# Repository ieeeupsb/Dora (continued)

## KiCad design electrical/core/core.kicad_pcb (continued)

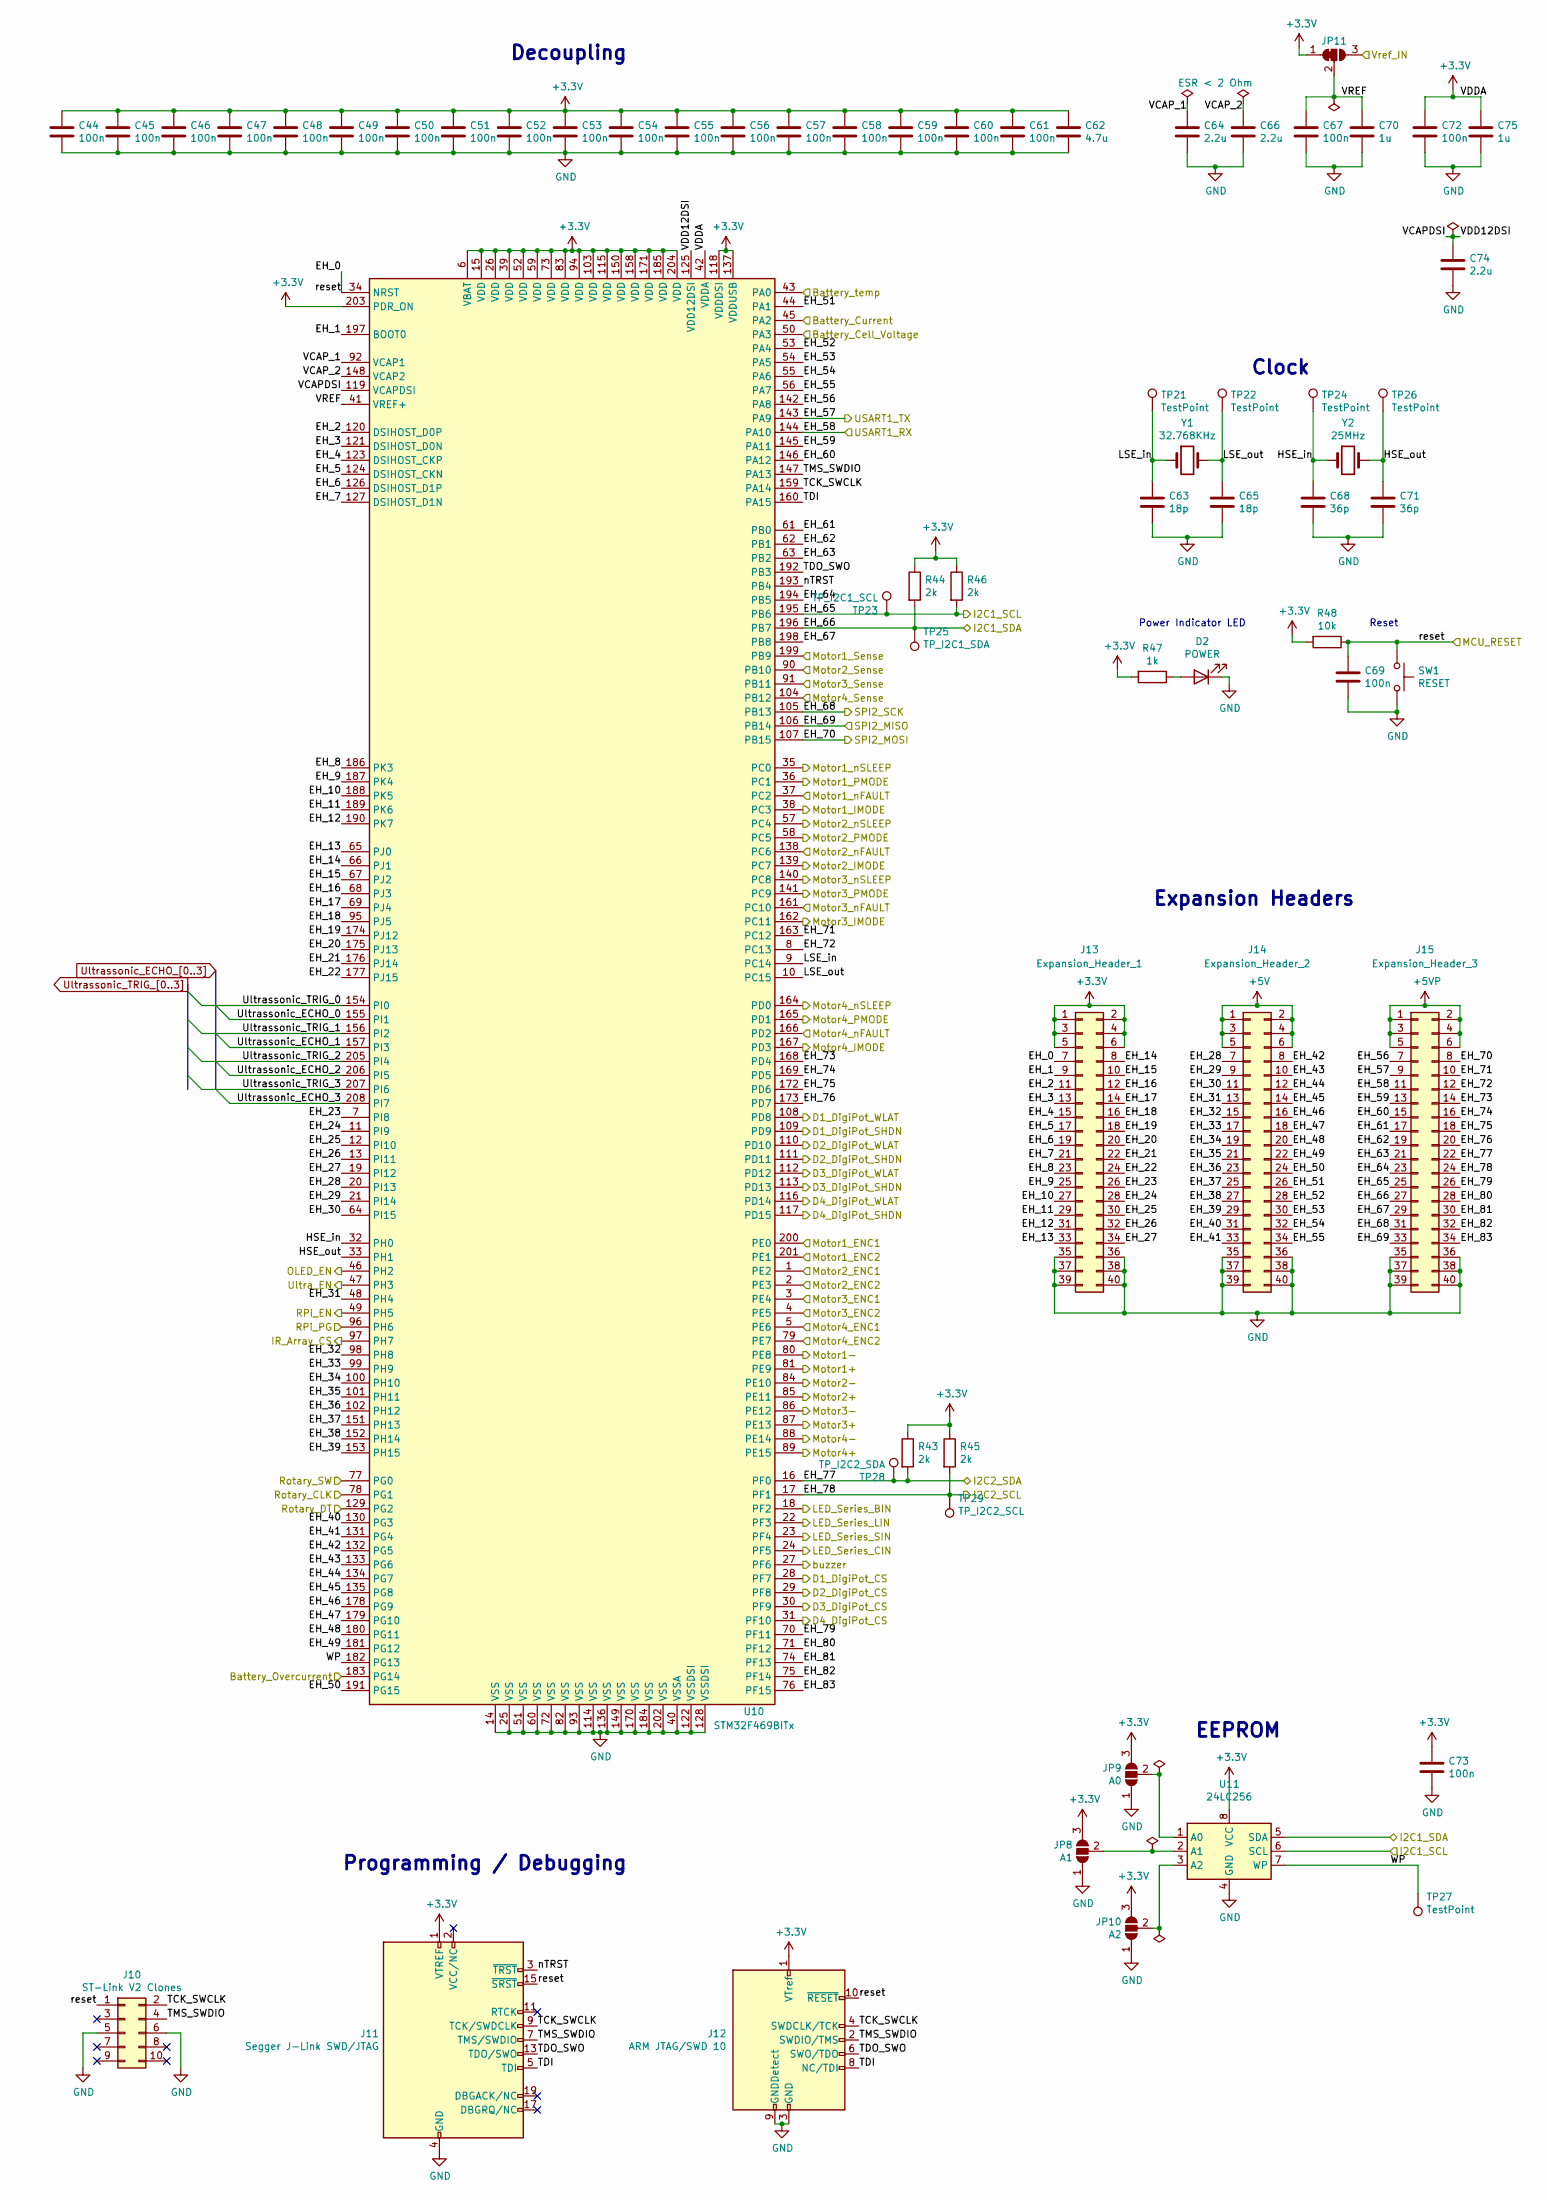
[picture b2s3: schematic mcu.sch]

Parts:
C44, C45, C46, C47, C48, C49, C50, C51, C52, C53, C54, C55, C56, C57, C58, C59, C60, C61, C67, C69, C72, C73: 100n; C_0603_1608Metric
C62: 4.7u; C_0603_1608Metric
C63, C65: 18p; C_0603_1608Metric
C64, C66, C74: 2.2u; C_0603_1608Metric
C68, C71: 36p; C_0603_1608Metric
C70, C75: 1u; C_0603_1608Metric
D2: POWER; LED_0805_2012Metric
J10: ST-Link V2 Clones; IDC-Header_2x05_P2.54mm_Vertical
J11: Segger J-Link SWD/JTAG; IDC-Header_2x10_P2.54mm_Vertical
J12: ARM JTAG/SWD 10; IDC-Header_2x05_P2.54mm_Vertical
J13: Expansion_Header_1; IDC-Header_2x20_P2.54mm_Vertical
J14: Expansion_Header_2; IDC-Header_2x20_P2.54mm_Vertical
J15: Expansion_Header_3; IDC-Header_2x20_P2.54mm_Vertical
JP8: A1; SolderJumper-3_P1.3mm_Open_Pad1.0x1.5mm
JP9: A0; SolderJumper-3_P1.3mm_Open_Pad1.0x1.5mm
JP10: A2; SolderJumper-3_P1.3mm_Open_Pad1.0x1.5mm
JP11: Vref_select; SolderJumper-3_P1.3mm_Bridged12_RoundedPad1.0x1.5mm_NumberL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
R43, R44, R45, R46: 2k; R_0603_1608Metric
R47: 1k; R_0603_1608Metric
R48: 10k; R_0603_1608Metric
SW1: RESET; SW_PUSH_6mm
TP21, TP22, TP24, TP26, TP27: TestPoint; TestPoint_Pad_D1.0mm
TP23: TP_I2C1_SCL; TestPoint_Pad_D1.0mm
TP25: TP_I2C1_SDA; TestPoint_Pad_D1.0mm
TP28: TP_I2C2_SDA; TestPoint_Pad_D1.0mm
TP29: TP_I2C2_SCL; TestPoint_Pad_D1.0mm
U10: STM32F469BITx; LQFP-208_28x28mm_P0.5mm
U11: 24LC256; SOIC-8_3.9x4.9mm_P1.27mm
Y1: 32.768KHz; Crystal_SMD_2520-4Pin_2.5x2.0mm
Y2: 25MHz; Crystal_SMD_2520-4Pin_2.5x2.0mm

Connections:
+3V3: C44.1, C45.1, C46.1, C47.1, C48.1, C49.1, C50.1, C51.1, C52.1, C53.1, C54.1, C55.1, C56.1, C57.1, C58.1, C59.1, C60.1, C61.1, C62.1, C72.1, C73.1, C75.1, J11.1 (VTREF), J12.1 (VTref), J13.1, J13.2, J13.3, J13.4, J13.5, J13.6, JP8.3 (B), JP9.3 (B), JP10.3 (B), JP11.1 (A), R43.1, R44.1, R45.1, R46.1, R47.2, R48.2, U10.6 (VBAT), U10.15 (VDD), U10.26 (VDD), U10.39 (VDD), U10.42 (VDDA), U10.52 (VDD), U10.59 (VDD), U10.73 (VDD), U10.83 (VDD), U10.94 (VDD), U10.103 (VDD), U10.115 (VDD), U10.118 (VDDDSI), U10.137 (VDDUSB), U10.150 (VDD), U10.158 (VDD), U10.171 (VDD), U10.185 (VDD), U10.203 (PDR_ON), U10.204 (VDD), U11.8 (VCC); also elsewhere on the board
+5V: J14.1, J14.2, J14.3, J14.4, J14.5, J14.6; also elsewhere on the board
+5VP: J15.1, J15.2, J15.3, J15.4, J15.5, J15.6; also elsewhere on the board
/Battery_Cell_Voltage: U10.50 (PA3); also elsewhere on the board
/Battery_Current: U10.45 (PA2); also elsewhere on the board
/Battery_Overcurrent: U10.183 (PG14); also elsewhere on the board
/Battery_Temperature: U10.43 (PA0); also elsewhere on the board
/D1_DigiPot_CS: U10.28 (PF7); also elsewhere on the board
/D1_DigiPot_SHDN: U10.109 (PD9); also elsewhere on the board
/D1_DigiPot_WLAT: U10.108 (PD8); also elsewhere on the board
/D1_IMODE: U10.38 (PC3); also elsewhere on the board
/D1_IN1: U10.80 (PE8); also elsewhere on the board
/D1_IN2: U10.81 (PE9); also elsewhere on the board
/D1_PMODE: U10.36 (PC1); also elsewhere on the board
/D1_SENSE: U10.199 (PB9); also elsewhere on the board
/D1_nFAULT: U10.37 (PC2); also elsewhere on the board
/D1_nSLEEP: U10.35 (PC0); also elsewhere on the board
/D2_DigiPot_CS: U10.29 (PF8); also elsewhere on the board
/D2_DigiPot_SHDN: U10.111 (PD11); also elsewhere on the board
/D2_DigiPot_WLAT: U10.110 (PD10); also elsewhere on the board
/D2_IMODE: U10.139 (PC7); also elsewhere on the board
/D2_IN1: U10.84 (PE10); also elsewhere on the board
/D2_IN2: U10.85 (PE11); also elsewhere on the board
/D2_PMODE: U10.58 (PC5); also elsewhere on the board
/D2_SENSE: U10.90 (PB10); also elsewhere on the board
/D2_nFAULT: U10.138 (PC6); also elsewhere on the board
/D2_nSLEEP: U10.57 (PC4); also elsewhere on the board
/D3_DigiPot_CS: U10.30 (PF9); also elsewhere on the board
/D3_DigiPot_SHDN: U10.113 (PD13); also elsewhere on the board
/D3_DigiPot_WLAT: U10.112 (PD12); also elsewhere on the board
/D3_IMODE: U10.162 (PC11); also elsewhere on the board
/D3_IN1: U10.86 (PE12); also elsewhere on the board
/D3_IN2: U10.87 (PE13); also elsewhere on the board
/D3_PMODE: U10.141 (PC9); also elsewhere on the board
/D3_SENSE: U10.91 (PB11); also elsewhere on the board
/D3_nFAULT: U10.161 (PC10); also elsewhere on the board
/D3_nSLEEP: U10.140 (PC8); also elsewhere on the board
/D4_DigiPot_CS: U10.31 (PF10); also elsewhere on the board
/D4_DigiPot_SHDN: U10.117 (PD15); also elsewhere on the board
/D4_DigiPot_WLAT: U10.116 (PD14); also elsewhere on the board
/D4_IMODE: U10.167 (PD3); also elsewhere on the board
/D4_IN1: U10.88 (PE14); also elsewhere on the board
/D4_IN2: U10.89 (PE15); also elsewhere on the board
/D4_PMODE: U10.165 (PD1); also elsewhere on the board
/D4_SENSE: U10.104 (PB12); also elsewhere on the board
/D4_nFAULT: U10.166 (PD2); also elsewhere on the board
/D4_nSLEEP: U10.164 (PD0); also elsewhere on the board
/I2C1_SCL: J15.25, R46.2, TP23.1, U10.195 (PB6), U11.6 (SCL); also elsewhere on the board
/I2C1_SDA: J15.27, R44.2, TP25.1, U10.196 (PB7), U11.5 (SDA); also elsewhere on the board
/I2C2_SCL: J15.24, R45.2, TP29.1, U10.17 (PF1); also elsewhere on the board
/I2C2_SDA: J15.22, R43.2, TP28.1, U10.16 (PF0); also elsewhere on the board
/IR_Array_CS: U10.97 (PH7); also elsewhere on the board
/LED_Series_BIN: U10.18 (PF2); also elsewhere on the board
/LED_Series_CIN: U10.24 (PF5); also elsewhere on the board
/LED_Series_LIN: U10.22 (PF3); also elsewhere on the board
/LED_Series_SIN: U10.23 (PF4); also elsewhere on the board
/MCU/EH_1: J13.9, U10.197 (BOOT0)
/MCU/EH_2: J13.11, U10.120 (DSIHOST_D0P)
/MCU/EH_3: J13.13, U10.121 (DSIHOST_D0N)
/MCU/EH_4: J13.15, U10.123 (DSIHOST_CKP)
/MCU/EH_5: J13.17, U10.124 (DSIHOST_CKN)
/MCU/EH_6: J13.19, U10.126 (DSIHOST_D1P)
/MCU/EH_7: J13.21, U10.127 (DSIHOST_D1N)
/MCU/EH_8: J13.23, U10.186 (PK3)
/MCU/EH_9: J13.25, U10.187 (PK4)
/MCU/EH_10: J13.27, U10.188 (PK5)
/MCU/EH_11: J13.29, U10.189 (PK6)
/MCU/EH_12: J13.31, U10.190 (PK7)
/MCU/EH_13: J13.33, U10.65 (PJ0)
/MCU/EH_14: J13.8, U10.66 (PJ1)
/MCU/EH_15: J13.10, U10.67 (PJ2)
/MCU/EH_16: J13.12, U10.68 (PJ3)
/MCU/EH_17: J13.14, U10.69 (PJ4)
/MCU/EH_18: J13.16, U10.95 (PJ5)
/MCU/EH_19: J13.18, U10.174 (PJ12)
/MCU/EH_20: J13.20, U10.175 (PJ13)
/MCU/EH_21: J13.22, U10.176 (PJ14)
/MCU/EH_22: J13.24, U10.177 (PJ15)
/MCU/EH_23: J13.26, U10.7 (PI8)
/MCU/EH_24: J13.28, U10.11 (PI9)
/MCU/EH_25: J13.30, U10.12 (PI10)
/MCU/EH_26: J13.32, U10.13 (PI11)
/MCU/EH_27: J13.34, U10.19 (PI12)
/MCU/EH_28: J14.7, U10.20 (PI13)
/MCU/EH_29: J14.9, U10.21 (PI14)
/MCU/EH_30: J14.11, U10.64 (PI15)
/MCU/EH_31: J14.13, U10.48 (PH4)
/MCU/EH_32: J14.15, U10.98 (PH8)
/MCU/EH_33: J14.17, U10.99 (PH9)
/MCU/EH_34: J14.19, U10.100 (PH10)
/MCU/EH_35: J14.21, U10.101 (PH11)
/MCU/EH_36: J14.23, U10.102 (PH12)
/MCU/EH_37: J14.25, U10.151 (PH13)
/MCU/EH_38: J14.27, U10.152 (PH14)
/MCU/EH_39: J14.29, U10.153 (PH15)
/MCU/EH_40: J14.31, U10.130 (PG3)
/MCU/EH_41: J14.33, U10.131 (PG4)
/MCU/EH_42: J14.8, U10.132 (PG5)
/MCU/EH_43: J14.10, U10.133 (PG6)
/MCU/EH_44: J14.12, U10.134 (PG7)
/MCU/EH_45: J14.14, U10.135 (PG8)
/MCU/EH_46: J14.16, U10.178 (PG9)
/MCU/EH_47: J14.18, U10.179 (PG10)
/MCU/EH_48: J14.20, U10.180 (PG11)
/MCU/EH_49: J14.22, U10.181 (PG12)
/MCU/EH_50: J14.24, U10.191 (PG15)
/MCU/EH_51: J14.26, U10.44 (PA1)
/MCU/EH_52: J14.28, U10.53 (PA4)
/MCU/EH_53: J14.30, U10.54 (PA5)
/MCU/EH_54: J14.32, U10.55 (PA6)
/MCU/EH_55: J14.34, U10.56 (PA7)
/MCU/EH_56: J15.7, U10.142 (PA8)
/MCU/EH_59: J15.13, U10.145 (PA11)
/MCU/EH_60: J15.15, U10.146 (PA12)
/MCU/EH_61: J15.17, U10.61 (PB0)
/MCU/EH_62: J15.19, U10.62 (PB1)
/MCU/EH_63: J15.21, U10.63 (PB2)
/MCU/EH_64: J15.23, U10.194 (PB5)
/MCU/EH_67: J15.29, U10.198 (PB8)
/MCU/EH_71: J15.10, U10.163 (PC12)
/MCU/EH_72: J15.12, U10.8 (PC13)
/MCU/EH_73: J15.14, U10.168 (PD4)
/MCU/EH_74: J15.16, U10.169 (PD5)
/MCU/EH_75: J15.18, U10.172 (PD6)
/MCU/EH_76: J15.20, U10.173 (PD7)
/MCU/EH_79: J15.26, U10.70 (PF11)
/MCU/EH_80: J15.28, U10.71 (PF12)
/MCU/EH_81: J15.30, U10.74 (PF13)
/MCU/EH_82: J15.32, U10.75 (PF14)
/MCU/EH_83: J15.34, U10.76 (PF15)
/MCU/HSE_in: C68.1, TP24.1, U10.32 (PH0), Y2.1
/MCU/HSE_out: C71.1, TP26.1, U10.33 (PH1), Y2.2
/MCU/LSE_in: C63.1, TP21.1, U10.9 (PC14), Y1.1
/MCU/LSE_out: C65.1, TP22.1, U10.10 (PC15), Y1.2
/MCU/TCK_SWCLK: J10.2, J11.9 (TCK/SWDCLK), J12.4 (SWDCLK/TCK), U10.159 (PA14)
/MCU/TDI: J11.5 (TDI), J12.8 (NC/TDI), U10.160 (PA15)
/MCU/TDO_SWO: J11.13 (TDO/SWO), J12.6 (SWO/TDO), U10.192 (PB3)
/MCU/TMS_SWDIO: J10.4, J11.7 (TMS/SWDIO), J12.2 (SWDIO/TMS), U10.147 (PA13)
/MCU/VCAPDSI: C74.1, U10.119 (VCAPDSI), U10.125 (VDD12DSI)
/MCU/VCAP_1: C64.1, U10.92 (VCAP1)
/MCU/VCAP_2: C66.1, U10.148 (VCAP2)
/MCU/VREF: C67.1, C70.1, JP11.2 (C), U10.41 (VREF+)
/MCU/WP: TP27.1, U10.182 (PG13), U11.7 (WP)
/MCU/nTRST: J11.3 (~TRST~), U10.193 (PB4)
/MCU_RESET: C69.1, J10.1, J11.15 (~SRST~), J12.10 (~RESET~), J13.7, R48.1, SW1.1, U10.34 (NRST); also elsewhere on the board
/Motor1_ENC1: U10.200 (PE0); also elsewhere on the board
/Motor1_ENC2: U10.201 (PE1); also elsewhere on the board
/Motor2_ENC1: U10.1 (PE2); also elsewhere on the board
/Motor2_ENC2: U10.2 (PE3); also elsewhere on the board
/Motor3_ENC1: U10.3 (PE4); also elsewhere on the board
/Motor3_ENC2: U10.4 (PE5); also elsewhere on the board
/Motor4_ENC1: U10.5 (PE6); also elsewhere on the board
/Motor4_ENC2: U10.79 (PE7); also elsewhere on the board
/OLED_EN: U10.46 (PH2); also elsewhere on the board
/RPi_EN: U10.49 (PH5); also elsewhere on the board
/RPi_PG: U10.96 (PH6); also elsewhere on the board
/RPi_RX: J15.9, U10.143 (PA9); also elsewhere on the board
/RPi_TX: J15.11, U10.144 (PA10); also elsewhere on the board
/Rotary_CLK: U10.78 (PG1); also elsewhere on the board
/Rotary_DT: U10.129 (PG2); also elsewhere on the board
/Rotary_SW: U10.77 (PG0); also elsewhere on the board
/SPI2_MISO: J15.33, U10.106 (PB14); also elsewhere on the board
/SPI2_MOSI: J15.8, U10.107 (PB15); also elsewhere on the board
/SPI2_SCK: J15.31, U10.105 (PB13); also elsewhere on the board
/Ultra_EN: U10.47 (PH3); also elsewhere on the board
/Vref_opt: JP11.3 (B); also elsewhere on the board
/buzzer: U10.27 (PF6); also elsewhere on the board
GND: C44.2, C45.2, C46.2, C47.2, C48.2, C49.2, C50.2, C51.2, C52.2, C53.2, C54.2, C55.2, C56.2, C57.2, C58.2, C59.2, C60.2, C61.2, C62.2, C63.2, C64.2, C65.2, C66.2, C67.2, C68.2, C69.2, C70.2, C71.2, C72.2, C73.2, C74.2, C75.2, D2.1 (K), J10.5, J10.6, J11.4 (GND), J11.6 (GND), J11.8 (GND), J11.10 (GND), J11.12 (GND), J11.14 (GND), J11.16 (GND), J11.18 (GND), J11.20 (GND), J12.3 (GND), J12.5 (GND), J12.9 (GNDDetect), J13.35, J13.36, J13.37, J13.38, J13.39, J13.40, J14.35, J14.36, J14.37, J14.38, J14.39, J14.40, J15.35, J15.36, J15.37, J15.38, J15.39, J15.40, JP8.1 (A), JP9.1 (A), JP10.1 (A), SW1.2, U10.14 (VSS), U10.25 (VSS), U10.40 (VSSA), U10.51 (VSS), U10.60 (VSS), U10.72 (VSS), U10.82 (VSS), U10.93 (VSS), U10.114 (VSS), U10.122 (VSSDSI), U10.128 (VSSDSI), U10.136 (VSS), U10.149 (VSS), U10.170 (VSS), U10.184 (VSS), U10.202 (VSS), U11.4 (GND); also elsewhere on the board
unnamed: D2.2 (A), R47.1
unnamed: JP8.2 (C), U11.2 (A1)
unnamed: JP9.2 (C), U11.1 (A0)
unnamed: JP10.2 (C), U11.3 (A2)
Ultrassonic_ECHO_0: U10.155 (PI1); also elsewhere on the board
Ultrassonic_ECHO_1: U10.157 (PI3); also elsewhere on the board
Ultrassonic_ECHO_2: U10.206 (PI5); also elsewhere on the board
Ultrassonic_ECHO_3: U10.208 (PI7); also elsewhere on the board
Ultrassonic_TRIG_0: U10.154 (PI0); also elsewhere on the board
Ultrassonic_TRIG_1: U10.156 (PI2); also elsewhere on the board
Ultrassonic_TRIG_2: U10.205 (PI4); also elsewhere on the board
Ultrassonic_TRIG_3: U10.207 (PI6); also elsewhere on the board

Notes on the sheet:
Decoupling
Clock
Programming / Debugging
EEPROM
Reset
Power Indicator LED
Expansion Headers

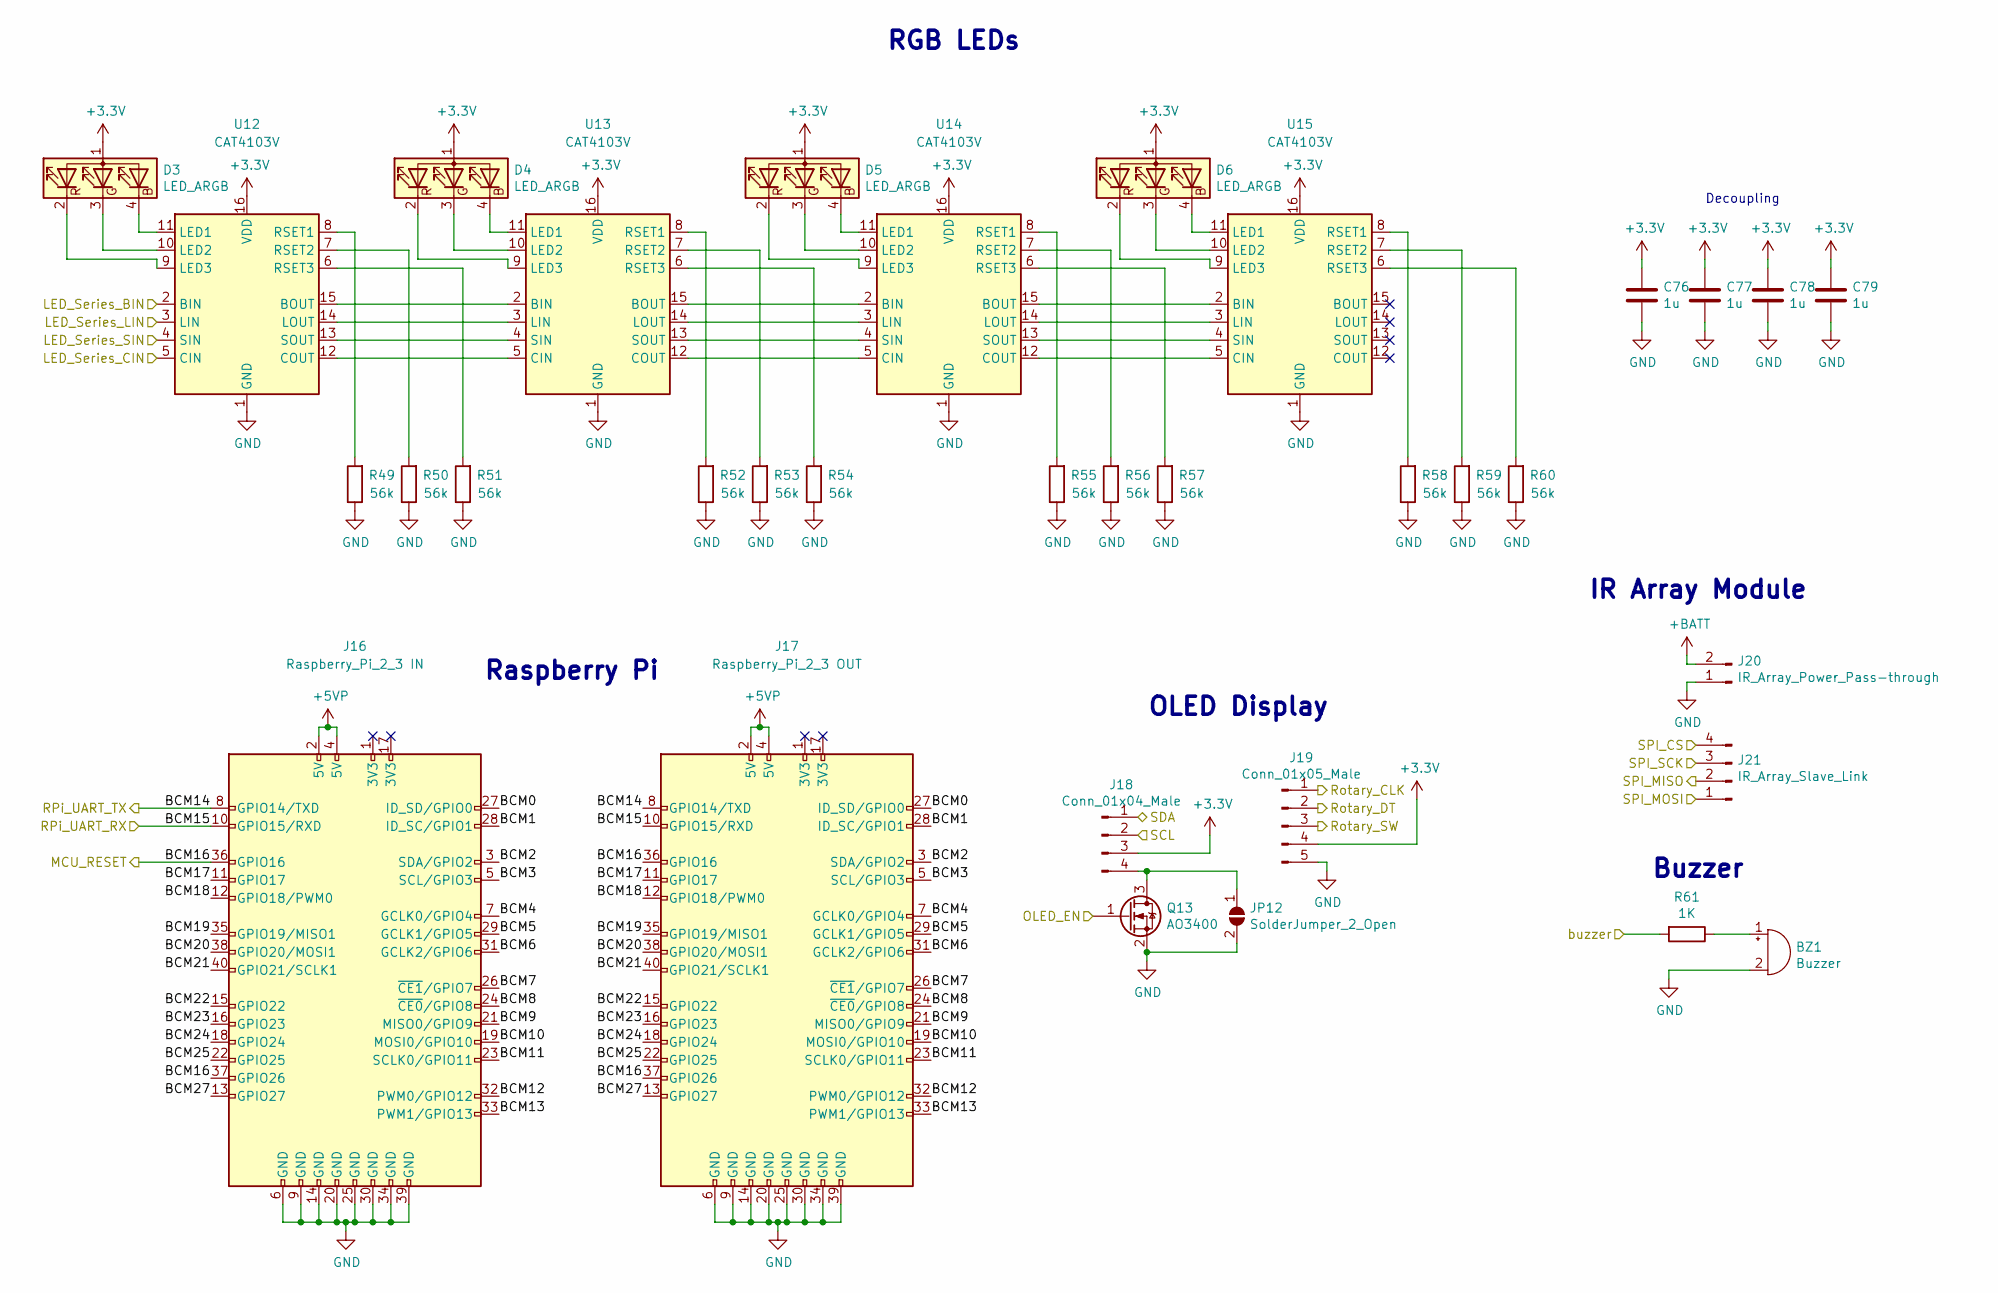
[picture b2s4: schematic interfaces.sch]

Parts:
BZ1: Buzzer; Buzzer_12x9.5RM7.6
C76, C77, C78, C79: 1u; C_0603_1608Metric
D3, D4, D5, D6: LED_ARGB; JST_XH_B4B-XH-A_1x04_P2.50mm_Vertical
J16: Raspberry_Pi_2_3 IN; IDC-Header_2x20_P2.54mm_Vertical
J17: Raspberry_Pi_2_3 OUT; IDC-Header_2x20_P2.54mm_Vertical
J18: Conn_01x04_Male; PinHeader_1x04_P2.54mm_Vertical
J19: Conn_01x05_Male; PinHeader_1x05_P2.54mm_Vertical
J20: IR_Array_Power_Pass-through; JST_XH_S2B-XH-A-1_1x02_P2.50mm_Horizontal
J21: IR_Array_Slave_Link; PinHeader_1x04_P2.54mm_Vertical
JP12: SolderJumper_2_Open; SolderJumper-2_P1.3mm_Open_Pad1.0x1.5mm
Q13: AO3400; SOT-23
R49, R50, R51, R52, R53, R54, R55, R56, R57, R58, R59, R60: 56k; R_0603_1608Metric
R61: 1K; R_0603_1608Metric
U12, U13, U14, U15: CAT4103V; SOIC-16_3.9x9.9mm_P1.27mm

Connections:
+3V3: C76.1, C77.1, C78.1, C79.1, D3.1 (A), D4.1 (A), D5.1 (A), D6.1 (A), J18.3, J19.4, U12.16 (VDD), U13.16 (VDD), U14.16 (VDD), U15.16 (VDD); also elsewhere on the board
+5VP: J16.2 (5V), J16.4 (5V), J17.2 (5V), J17.4 (5V); also elsewhere on the board
+BATT: J20.2; also elsewhere on the board
/I2C1_SCL: J18.2; also elsewhere on the board
/I2C1_SDA: J18.1; also elsewhere on the board
/IR_Array_CS: J21.4; also elsewhere on the board
/Interfaces/BCM0: J16.27 (ID_SD/GPIO0), J17.27 (ID_SD/GPIO0)
/Interfaces/BCM1: J16.28 (ID_SC/GPIO1), J17.28 (ID_SC/GPIO1)
/Interfaces/BCM2: J16.3 (SDA/GPIO2), J17.3 (SDA/GPIO2)
/Interfaces/BCM3: J16.5 (SCL/GPIO3), J17.5 (SCL/GPIO3)
/Interfaces/BCM4: J16.7 (GCLK0/GPIO4), J17.7 (GCLK0/GPIO4)
/Interfaces/BCM5: J16.29 (GCLK1/GPIO5), J17.29 (GCLK1/GPIO5)
/Interfaces/BCM6: J16.31 (GCLK2/GPIO6), J17.31 (GCLK2/GPIO6)
/Interfaces/BCM7: J16.26 (~CE1~/GPIO7), J17.26 (~CE1~/GPIO7)
/Interfaces/BCM8: J16.24 (~CE0~/GPIO8), J17.24 (~CE0~/GPIO8)
/Interfaces/BCM9: J16.21 (MISO0/GPIO9), J17.21 (MISO0/GPIO9)
/Interfaces/BCM10: J16.19 (MOSI0/GPIO10), J17.19 (MOSI0/GPIO10)
/Interfaces/BCM11: J16.23 (SCLK0/GPIO11), J17.23 (SCLK0/GPIO11)
/Interfaces/BCM12: J16.32 (PWM0/GPIO12), J17.32 (PWM0/GPIO12)
/Interfaces/BCM13: J16.33 (PWM1/GPIO13), J17.33 (PWM1/GPIO13)
/Interfaces/BCM17: J16.11 (GPIO17), J17.11 (GPIO17)
/Interfaces/BCM18: J16.12 (GPIO18/PWM0), J17.12 (GPIO18/PWM0)
/Interfaces/BCM19: J16.35 (GPIO19/MISO1), J17.35 (GPIO19/MISO1)
/Interfaces/BCM20: J16.38 (GPIO20/MOSI1), J17.38 (GPIO20/MOSI1)
/Interfaces/BCM21: J16.40 (GPIO21/SCLK1), J17.40 (GPIO21/SCLK1)
/Interfaces/BCM22: J16.15 (GPIO22), J17.15 (GPIO22)
/Interfaces/BCM23: J16.16 (GPIO23), J17.16 (GPIO23)
/Interfaces/BCM24: J16.18 (GPIO24), J17.18 (GPIO24)
/Interfaces/BCM25: J16.22 (GPIO25), J17.22 (GPIO25)
/Interfaces/BCM27: J16.13 (GPIO27), J17.13 (GPIO27)
/LED_Series_BIN: U12.2 (BIN); also elsewhere on the board
/LED_Series_CIN: U12.5 (CIN); also elsewhere on the board
/LED_Series_LIN: U12.3 (LIN); also elsewhere on the board
/LED_Series_SIN: U12.4 (SIN); also elsewhere on the board
/MCU_RESET: J16.36 (GPIO16), J16.37 (GPIO26), J17.36 (GPIO16), J17.37 (GPIO26); also elsewhere on the board
/OLED_EN: Q13.1 (G); also elsewhere on the board
/RPi_RX: J16.10 (GPIO15/RXD), J17.10 (GPIO15/RXD); also elsewhere on the board
/RPi_TX: J16.8 (GPIO14/TXD), J17.8 (GPIO14/TXD); also elsewhere on the board
/Rotary_CLK: J19.1; also elsewhere on the board
/Rotary_DT: J19.2; also elsewhere on the board
/Rotary_SW: J19.3; also elsewhere on the board
/SPI2_MISO: J21.2; also elsewhere on the board
/SPI2_MOSI: J21.1; also elsewhere on the board
/SPI2_SCK: J21.3; also elsewhere on the board
/buzzer: R61.2; also elsewhere on the board
GND: BZ1.2 (+), C76.2, C77.2, C78.2, C79.2, J16.6 (GND), J16.9 (GND), J16.14 (GND), J16.20 (GND), J16.25 (GND), J16.30 (GND), J16.34 (GND), J16.39 (GND), J17.6 (GND), J17.9 (GND), J17.14 (GND), J17.20 (GND), J17.25 (GND), J17.30 (GND), J17.34 (GND), J17.39 (GND), J19.5, J20.1, JP12.2 (B), Q13.2 (S), R49.1, R50.1, R51.1, R52.1, R53.1, R54.1, R55.1, R56.1, R57.1, R58.1, R59.1, R60.1, U12.1 (GND), U13.1 (GND), U14.1 (GND), U15.1 (GND); also elsewhere on the board
unnamed: BZ1.1 (-), R61.1
unnamed: D3.2 (RK), U12.9 (LED3)
unnamed: D3.3 (GK), U12.10 (LED2)
unnamed: D3.4 (BK), U12.11 (LED1)
unnamed: D4.2 (RK), U13.9 (LED3)
unnamed: D4.3 (GK), U13.10 (LED2)
unnamed: D4.4 (BK), U13.11 (LED1)
unnamed: D5.2 (RK), U14.9 (LED3)
unnamed: D5.3 (GK), U14.10 (LED2)
unnamed: D5.4 (BK), U14.11 (LED1)
unnamed: D6.2 (RK), U15.9 (LED3)
unnamed: D6.3 (GK), U15.10 (LED2)
unnamed: D6.4 (BK), U15.11 (LED1)
unnamed: J18.4, JP12.1 (A), Q13.3 (D)
unnamed: R49.2, U12.8 (RSET1)
unnamed: R50.2, U12.7 (RSET2)
unnamed: R51.2, U12.6 (RSET3)
unnamed: R52.2, U13.8 (RSET1)
unnamed: R53.2, U13.7 (RSET2)
unnamed: R54.2, U13.6 (RSET3)
unnamed: R55.2, U14.8 (RSET1)
unnamed: R56.2, U14.7 (RSET2)
unnamed: R57.2, U14.6 (RSET3)
unnamed: R58.2, U15.8 (RSET1)
unnamed: R59.2, U15.7 (RSET2)
unnamed: R60.2, U15.6 (RSET3)
unnamed: U12.12 (COUT), U13.5 (CIN)
unnamed: U12.13 (SOUT), U13.4 (SIN)
unnamed: U12.14 (LOUT), U13.3 (LIN)
unnamed: U12.15 (BOUT), U13.2 (BIN)
unnamed: U13.12 (COUT), U14.5 (CIN)
unnamed: U13.13 (SOUT), U14.4 (SIN)
unnamed: U13.14 (LOUT), U14.3 (LIN)
unnamed: U13.15 (BOUT), U14.2 (BIN)
unnamed: U14.12 (COUT), U15.5 (CIN)
unnamed: U14.13 (SOUT), U15.4 (SIN)
unnamed: U14.14 (LOUT), U15.3 (LIN)
unnamed: U14.15 (BOUT), U15.2 (BIN)

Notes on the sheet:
Buzzer
RGB LEDs
OLED Display
Raspberry Pi
Decoupling
IR Array Module

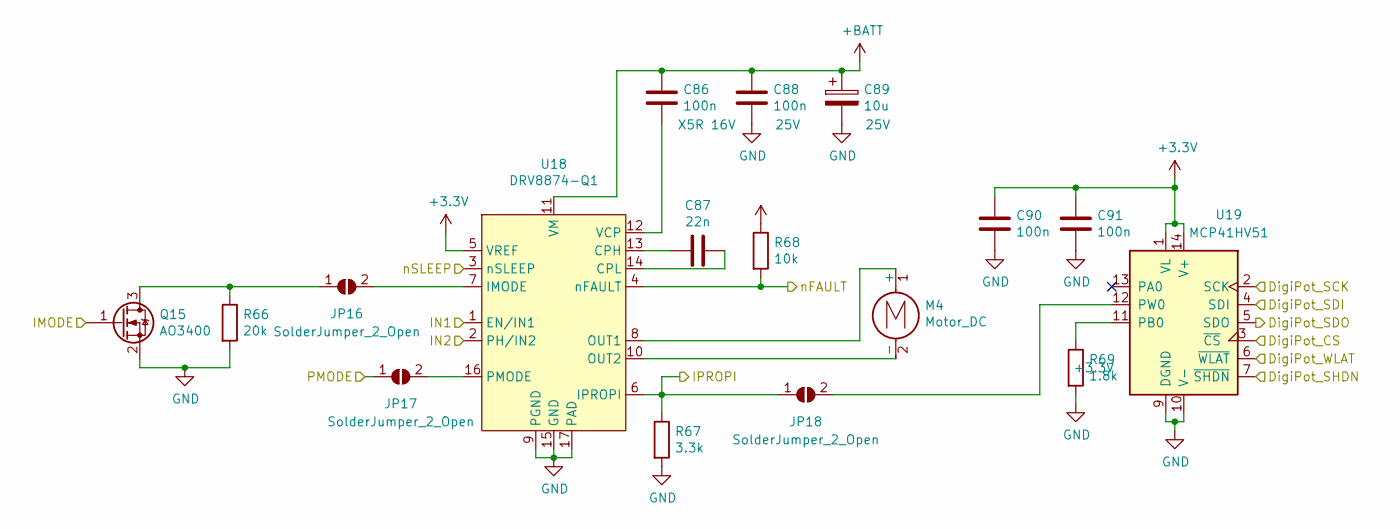
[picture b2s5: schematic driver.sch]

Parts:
C1, C3: 100n; C_1206_3216Metric
C2: 22n; C_1206_3216Metric
C4: 10u; CP_Elec_5x5.4
C5, C6: 100n; C_0603_1608Metric
JP1, JP2, JP3: SolderJumper_2_Open; SolderJumper-2_P1.3mm_Open_Pad1.0x1.5mm
M1: Motor_DC; TerminalBlock_bornier-2_P5.08mm
Q1: AO3400; SOT-23
R1: 20k; R_0603_1608Metric
R2: 3.3k; R_0603_1608Metric
R3: 10k; R_0603_1608Metric
R4: 1.8k; R_0603_1608Metric
U1: DRV8874-Q1; HTSSOP-16-1EP_4.4x5mm_P0.65mm_EP3.4x5mm_Mask2.46x2.31mm_The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
U2: MCP41HV51; TSSOP-14_4.4x5mm_P0.65mm

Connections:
+3V3: C5.1, C6.1, R3.1, U1.5 (VREF), U2.1 (VL), U2.14 (V+); also elsewhere on the board
+BATT: C1.1, C3.1, C4.1, U1.11 (VM); also elsewhere on the board
/D1_DigiPot_CS: U2.3 (~CS); also elsewhere on the board
/D1_DigiPot_SHDN: U2.7 (~SHDN); also elsewhere on the board
/D1_DigiPot_WLAT: U2.6 (~WLAT); also elsewhere on the board
/D1_IMODE: Q1.1 (G); also elsewhere on the board
/D1_IN1: U1.1 (EN/IN1); also elsewhere on the board
/D1_IN2: U1.2 (PH/IN2); also elsewhere on the board
/D1_PMODE: JP2.1 (A); also elsewhere on the board
/D1_SENSE: JP3.1 (A), R2.1, U1.6 (IPROPI); also elsewhere on the board
/D1_nFAULT: R3.2, U1.4 (nFAULT); also elsewhere on the board
/D1_nSLEEP: U1.3 (nSLEEP); also elsewhere on the board
/SPI2_MISO: U2.5 (SDO); also elsewhere on the board
/SPI2_MOSI: U2.4 (SDI); also elsewhere on the board
/SPI2_SCK: U2.2 (SCK); also elsewhere on the board
GND: C3.2, C4.2, C5.2, C6.2, Q1.2 (S), R1.2, R2.2, R4.2, U1.9 (PGND), U1.15 (GND), U1.17 (PAD), U2.9 (DGND), U2.10 (V-); also elsewhere on the board
unnamed: C1.2, U1.12 (VCP)
unnamed: C2.1, U1.14 (CPL)
unnamed: C2.2, U1.13 (CPH)
unnamed: JP1.1 (A), Q1.3 (D), R1.1
unnamed: JP1.2 (B), U1.7 (IMODE)
unnamed: JP2.2 (B), U1.16 (PMODE)
unnamed: JP3.2 (B), U2.12 (PW0)
unnamed: M1.1 (+), U1.8 (OUT1)
unnamed: M1.2 (-), U1.10 (OUT2)
unnamed: R4.1, U2.11 (PB0)

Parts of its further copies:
C7, C9, C80, C82, C86, C88: 100n; C_1206_3216Metric
C8, C81, C87: 22n; C_1206_3216Metric
C10, C83, C89: 10u; CP_Elec_5x5.4
C11, C12, C84, C85, C90, C91: 100n; C_0603_1608Metric
JP4, JP5, JP6, JP13, JP14, JP15, JP16, JP17, JP18: SolderJumper_2_Open; SolderJumper-2_P1.3mm_Open_Pad1.0x1.5mm
M2, M3, M4: Motor_DC; TerminalBlock_bornier-2_P5.08mm
Q2, Q14, Q15: AO3400; SOT-23
R5, R62, R66: 20k; R_0603_1608Metric
R6, R63, R67: 3.3k; R_0603_1608Metric
R7, R64, R68: 10k; R_0603_1608Metric
R8, R65, R69: 1.8k; R_0603_1608Metric
U3, U16, U18: DRV8874-Q1; HTSSOP-16-1EP_4.4x5mm_P0.65mm_EP3.4x5mm_Mask2.46x2.31mm_The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
U4, U17, U19: MCP41HV51; TSSOP-14_4.4x5mm_P0.65mm

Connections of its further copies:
+3V3: C11.1, C12.1, C84.1, C85.1, C90.1, C91.1, R7.1, R64.1, R68.1, U3.5 (VREF), U4.1 (VL), U4.14 (V+), U16.5 (VREF), U17.1 (VL), U17.14 (V+), U18.5 (VREF), U19.1 (VL), U19.14 (V+); also elsewhere on the board
+BATT: C7.1, C9.1, C10.1, C80.1, C82.1, C83.1, C86.1, C88.1, C89.1, U3.11 (VM), U16.11 (VM), U18.11 (VM); also elsewhere on the board
/D2_DigiPot_CS: U4.3 (~CS); also elsewhere on the board
/D2_DigiPot_SHDN: U4.7 (~SHDN); also elsewhere on the board
/D2_DigiPot_WLAT: U4.6 (~WLAT); also elsewhere on the board
/D2_IMODE: Q2.1 (G); also elsewhere on the board
/D2_IN1: U3.1 (EN/IN1); also elsewhere on the board
/D2_IN2: U3.2 (PH/IN2); also elsewhere on the board
/D2_PMODE: JP5.1 (A); also elsewhere on the board
/D2_SENSE: JP6.1 (A), R6.1, U3.6 (IPROPI); also elsewhere on the board
/D2_nFAULT: R7.2, U3.4 (nFAULT); also elsewhere on the board
/D2_nSLEEP: U3.3 (nSLEEP); also elsewhere on the board
/D3_DigiPot_CS: U17.3 (~CS); also elsewhere on the board
/D3_DigiPot_SHDN: U17.7 (~SHDN); also elsewhere on the board
/D3_DigiPot_WLAT: U17.6 (~WLAT); also elsewhere on the board
/D3_IMODE: Q14.1 (G); also elsewhere on the board
/D3_IN1: U16.1 (EN/IN1); also elsewhere on the board
/D3_IN2: U16.2 (PH/IN2); also elsewhere on the board
/D3_PMODE: JP14.1 (A); also elsewhere on the board
/D3_SENSE: JP15.1 (A), R63.1, U16.6 (IPROPI); also elsewhere on the board
/D3_nFAULT: R64.2, U16.4 (nFAULT); also elsewhere on the board
/D3_nSLEEP: U16.3 (nSLEEP); also elsewhere on the board
/D4_DigiPot_CS: U19.3 (~CS); also elsewhere on the board
/D4_DigiPot_SHDN: U19.7 (~SHDN); also elsewhere on the board
/D4_DigiPot_WLAT: U19.6 (~WLAT); also elsewhere on the board
/D4_IMODE: Q15.1 (G); also elsewhere on the board
/D4_IN1: U18.1 (EN/IN1); also elsewhere on the board
/D4_IN2: U18.2 (PH/IN2); also elsewhere on the board
/D4_PMODE: JP17.1 (A); also elsewhere on the board
/D4_SENSE: JP18.1 (A), R67.1, U18.6 (IPROPI); also elsewhere on the board
/D4_nFAULT: R68.2, U18.4 (nFAULT); also elsewhere on the board
/D4_nSLEEP: U18.3 (nSLEEP); also elsewhere on the board
/SPI2_MISO: U4.5 (SDO), U17.5 (SDO), U19.5 (SDO); also elsewhere on the board
/SPI2_MOSI: U4.4 (SDI), U17.4 (SDI), U19.4 (SDI); also elsewhere on the board
/SPI2_SCK: U4.2 (SCK), U17.2 (SCK), U19.2 (SCK); also elsewhere on the board
GND: C9.2, C10.2, C11.2, C12.2, C82.2, C83.2, C84.2, C85.2, C88.2, C89.2, C90.2, C91.2, Q2.2 (S), Q14.2 (S), Q15.2 (S), R5.2, R6.2, R8.2, R62.2, R63.2, R65.2, R66.2, R67.2, R69.2, U3.9 (PGND), U3.15 (GND), U3.17 (PAD), U4.9 (DGND), U4.10 (V-), U16.9 (PGND), U16.15 (GND), U16.17 (PAD), U17.9 (DGND), U17.10 (V-), U18.9 (PGND), U18.15 (GND), U18.17 (PAD), U19.9 (DGND), U19.10 (V-); also elsewhere on the board
unnamed: C7.2, U3.12 (VCP)
unnamed: C8.1, U3.14 (CPL)
unnamed: C8.2, U3.13 (CPH)
unnamed: C80.2, U16.12 (VCP)
unnamed: C81.1, U16.14 (CPL)
unnamed: C81.2, U16.13 (CPH)
unnamed: C86.2, U18.12 (VCP)
unnamed: C87.1, U18.14 (CPL)
unnamed: C87.2, U18.13 (CPH)
unnamed: JP4.1 (A), Q2.3 (D), R5.1
unnamed: JP4.2 (B), U3.7 (IMODE)
unnamed: JP5.2 (B), U3.16 (PMODE)
unnamed: JP6.2 (B), U4.12 (PW0)
unnamed: JP13.1 (A), Q14.3 (D), R62.1
unnamed: JP13.2 (B), U16.7 (IMODE)
unnamed: JP14.2 (B), U16.16 (PMODE)
unnamed: JP15.2 (B), U17.12 (PW0)
unnamed: JP16.1 (A), Q15.3 (D), R66.1
unnamed: JP16.2 (B), U18.7 (IMODE)
unnamed: JP17.2 (B), U18.16 (PMODE)
unnamed: JP18.2 (B), U19.12 (PW0)
unnamed: M2.1 (+), U3.8 (OUT1)
unnamed: M2.2 (-), U3.10 (OUT2)
unnamed: M3.1 (+), U16.8 (OUT1)
unnamed: M3.2 (-), U16.10 (OUT2)
unnamed: M4.1 (+), U18.8 (OUT1)
unnamed: M4.2 (-), U18.10 (OUT2)
unnamed: R8.1, U4.11 (PB0)
unnamed: R65.1, U17.11 (PB0)
unnamed: R69.1, U19.11 (PB0)

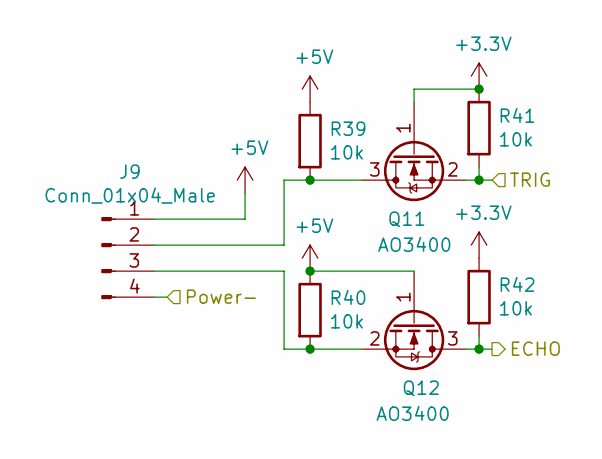
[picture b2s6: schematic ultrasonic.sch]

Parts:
J6: Conn_01x04_Male; PinHeader_1x04_P2.54mm_Vertical
Q5, Q6: AO3400; SOT-23
R27, R28, R29, R30: 10k; R_0603_1608Metric

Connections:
+3V3: Q5.1 (G), R29.1, R30.1; also elsewhere on the board
+5V: J6.1, Q6.1 (G), R27.1, R28.1; also elsewhere on the board
/Sensors/Ultrassonic_0/Power-: J6.4; also elsewhere on the board
unnamed: J6.2, Q5.3 (D), R27.2
unnamed: J6.3, Q6.2 (S), R28.2
Ultrassonic_ECHO_0: Q6.3 (D), R30.2; also elsewhere on the board
Ultrassonic_TRIG_0: Q5.2 (S), R29.2; also elsewhere on the board

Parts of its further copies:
J7, J8, J9: Conn_01x04_Male; PinHeader_1x04_P2.54mm_Vertical
Q7, Q8, Q9, Q10, Q11, Q12: AO3400; SOT-23
R31, R32, R33, R34, R35, R36, R37, R38, R39, R40, R41, R42: 10k; R_0603_1608Metric

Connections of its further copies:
+3V3: Q7.1 (G), Q9.1 (G), Q11.1 (G), R33.1, R34.1, R37.1, R38.1, R41.1, R42.1; also elsewhere on the board
+5V: J7.1, J8.1, J9.1, Q8.1 (G), Q10.1 (G), Q12.1 (G), R31.1, R32.1, R35.1, R36.1, R39.1, R40.1; also elsewhere on the board
/Sensors/Ultrassonic_0/Power-: J7.4, J8.4, J9.4; also elsewhere on the board
unnamed: J7.2, Q7.3 (D), R31.2
unnamed: J7.3, Q8.2 (S), R32.2
unnamed: J8.2, Q9.3 (D), R35.2
unnamed: J8.3, Q10.2 (S), R36.2
unnamed: J9.2, Q11.3 (D), R39.2
unnamed: J9.3, Q12.2 (S), R40.2
Ultrassonic_ECHO_1: Q8.3 (D), R34.2; also elsewhere on the board
Ultrassonic_ECHO_2: Q10.3 (D), R38.2; also elsewhere on the board
Ultrassonic_ECHO_3: Q12.3 (D), R42.2; also elsewhere on the board
Ultrassonic_TRIG_1: Q7.2 (S), R33.2; also elsewhere on the board
Ultrassonic_TRIG_2: Q9.2 (S), R37.2; also elsewhere on the board
Ultrassonic_TRIG_3: Q11.2 (S), R41.2; also elsewhere on the board
